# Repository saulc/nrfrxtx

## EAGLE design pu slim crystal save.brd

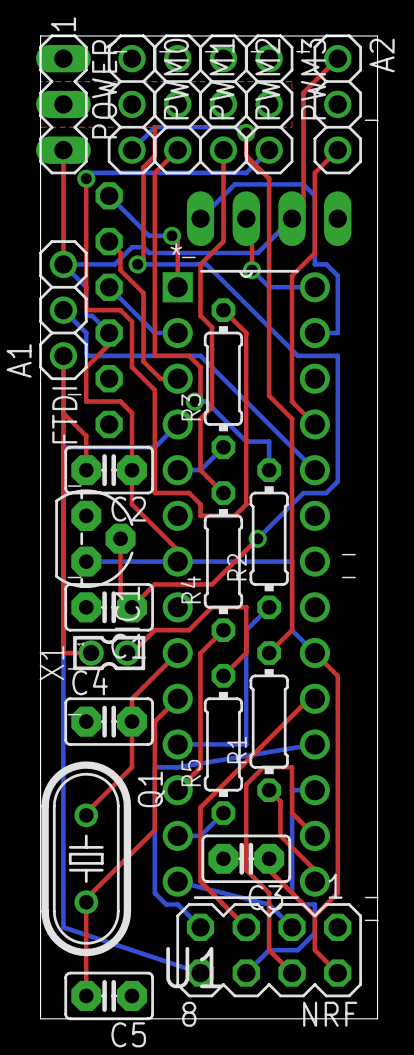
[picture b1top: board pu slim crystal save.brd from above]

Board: 2 copper layers, 18.7 x 54.6 mm, 24 parts (1 on the bottom side), 28 nets.

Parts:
A1, A2: 1X03
C1, C2: 1uf; C025-025X050
C3: 10uf; C025-025X050
C4, C5: 22pf; C025-025X050
FTDI: 1X06-CLEAN
I2C: MA04-1
IC1: TO92
NRF: MA04-2
POWER: MA03-1
PWM0, PWM1, PWM2, PWM3: 1X03
Q1: HC49U-V
R1, R2, R3, R4, R5: 0204/7
U1: ATMEGA328P-PU; DIP254P762X457-28
X1: 87758-0216

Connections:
3PWM: R3.1, U1.5
5PWM: R2.1, U1.11
6PWM: R4.1, U1.12
7: R5.2, X1.2
9PWM: R1.1, U1.15
10PWM: NRF.4, U1.16
A1: A1.2, U1.24
A2: A2.3, U1.25
CY6: C4.2, Q1.1, U1.9
CY7: C5.2, Q1.2, U1.10
D2: NRF.8, U1.4
D7: R5.1, U1.13
D8: NRF.3, U1.14
GND: A1.1, A2.2, C1.2, C2.2, C3.2, C4.1, C5.1, FTDI.1, I2C.1, IC1.1, NRF.1, POWER.1, PWM0.1, PWM1.1, PWM2.1, PWM3.1, U1.22, X1.1
MISO: NRF.7, U1.18
MOSI: NRF.6, U1.17
PWM0OUT: PWM0.3, R1.2
PWM1OUT: PWM1.3, R2.2
PWM2OUT: PWM2.3, R4.2
PWM3OUT: PWM3.3, R3.2
RST: FTDI.6, U1.1
RX: FTDI.4, U1.2
SCK: NRF.5, U1.19
SCL: I2C.3, U1.28
SDA: I2C.4, U1.27
TX: FTDI.5, U1.3
VCC: A1.3, A2.1, C2.1, C3.1, FTDI.3, I2C.2, IC1.3, NRF.2, POWER.3, U1.7, U1.20
VIN: C1.1, IC1.2, POWER.2, PWM0.2, PWM1.2, PWM2.2, PWM3.2

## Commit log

2017-05-11 first commit
    copied schematic, created black board
2017-07-17 update
    idk
2017-07-19 working
    adding status led on d4 or d7
2017-07-19 added status led on d7
    digital only. with resistor
